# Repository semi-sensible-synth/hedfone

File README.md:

# hedfone eurorack module

_Simple stereo sum fixed panning headphone output in 2HP_

## Features

A 2HP headphone output with:

- Left and right mono inputs at eurorack levels (left+left, right+right, summed)
- First set of inputs panned hard left/right, second set are 'soft' left/right by ~6dB in the stereo field
- A 3.5mm TRS stereo output at line/headphone levels (0.4x gain, 5V -> 2.1 Vpp output)
- Dual audio op-amps per output channel to drive headphones
- Volume adjustment knob
- Internal pin header to take input from other modules (eg a mixer)

Intended to be used with 0HP attenuators if one of the summed inputs needs to be mixed/panned, or a 0HP passive mult if you need to put a mono signal into both channels.

## Design

For the headphone output, I used design similar to [this headphone amplifier](http://www.redcircuits.com/Page155.htm) using a dual op-amp (NE5532) per channel. The first op amp unit acts as a unity gain buffer, with a second non-inverting op amp in parallel to the output acting as voltage follower/buffer to allow it to drive more current. Other modules that use a similar technique include the [Befaco Out v3](https://www.befaco.org/out-v3/) headphone driver or [Forest Caver's Headphone Amp module](https://github.com/forestcaver/Analog-Voice/tree/master/AJH_Headphone_Amp).

The 3.5mm TRS stereo jack can be a [green Thonkiconn PJ366ST](https://www.thonk.co.uk/shop/green-stereo-thonkiconn-jacks-pj366st-x1/) or a [Tayda A-6115](https://www.taydaelectronics.com/3-5mm-stereo-enclosed-socket.html) bodged with a resistor wire.

## Version 1.1.2 - TODO
_(fixes for next revision)_

- Pot direction is reversed.
- Outer L/R pair are hard panned, inner pair are soft panned. This wasn't intentional, but actually makes sense (more like Nearness) - swap inner pair order and front panel to reflect that (so we have top to bottom L/L/R/R with the outer jacks hard panned)

## Version 1.1.1

Fix footprint for D1,D2 (SOD-523 -> SOD-323)

## Version 1.1

Made the second set of inputs 'soft' panned left and right by ~6dB.
Removed left->right normalling for mono (can't easily co-exist with the soft panning feature)

## Version 1.0

Initial release to production.

## License

[CERN-OHL-S-2.0](https://ohwr.org/cern_ohl_s_v2.txt) (*CERN Open Hardware License Version 2 - Strongly Reciprocal*), Andrew Perry, 2023.

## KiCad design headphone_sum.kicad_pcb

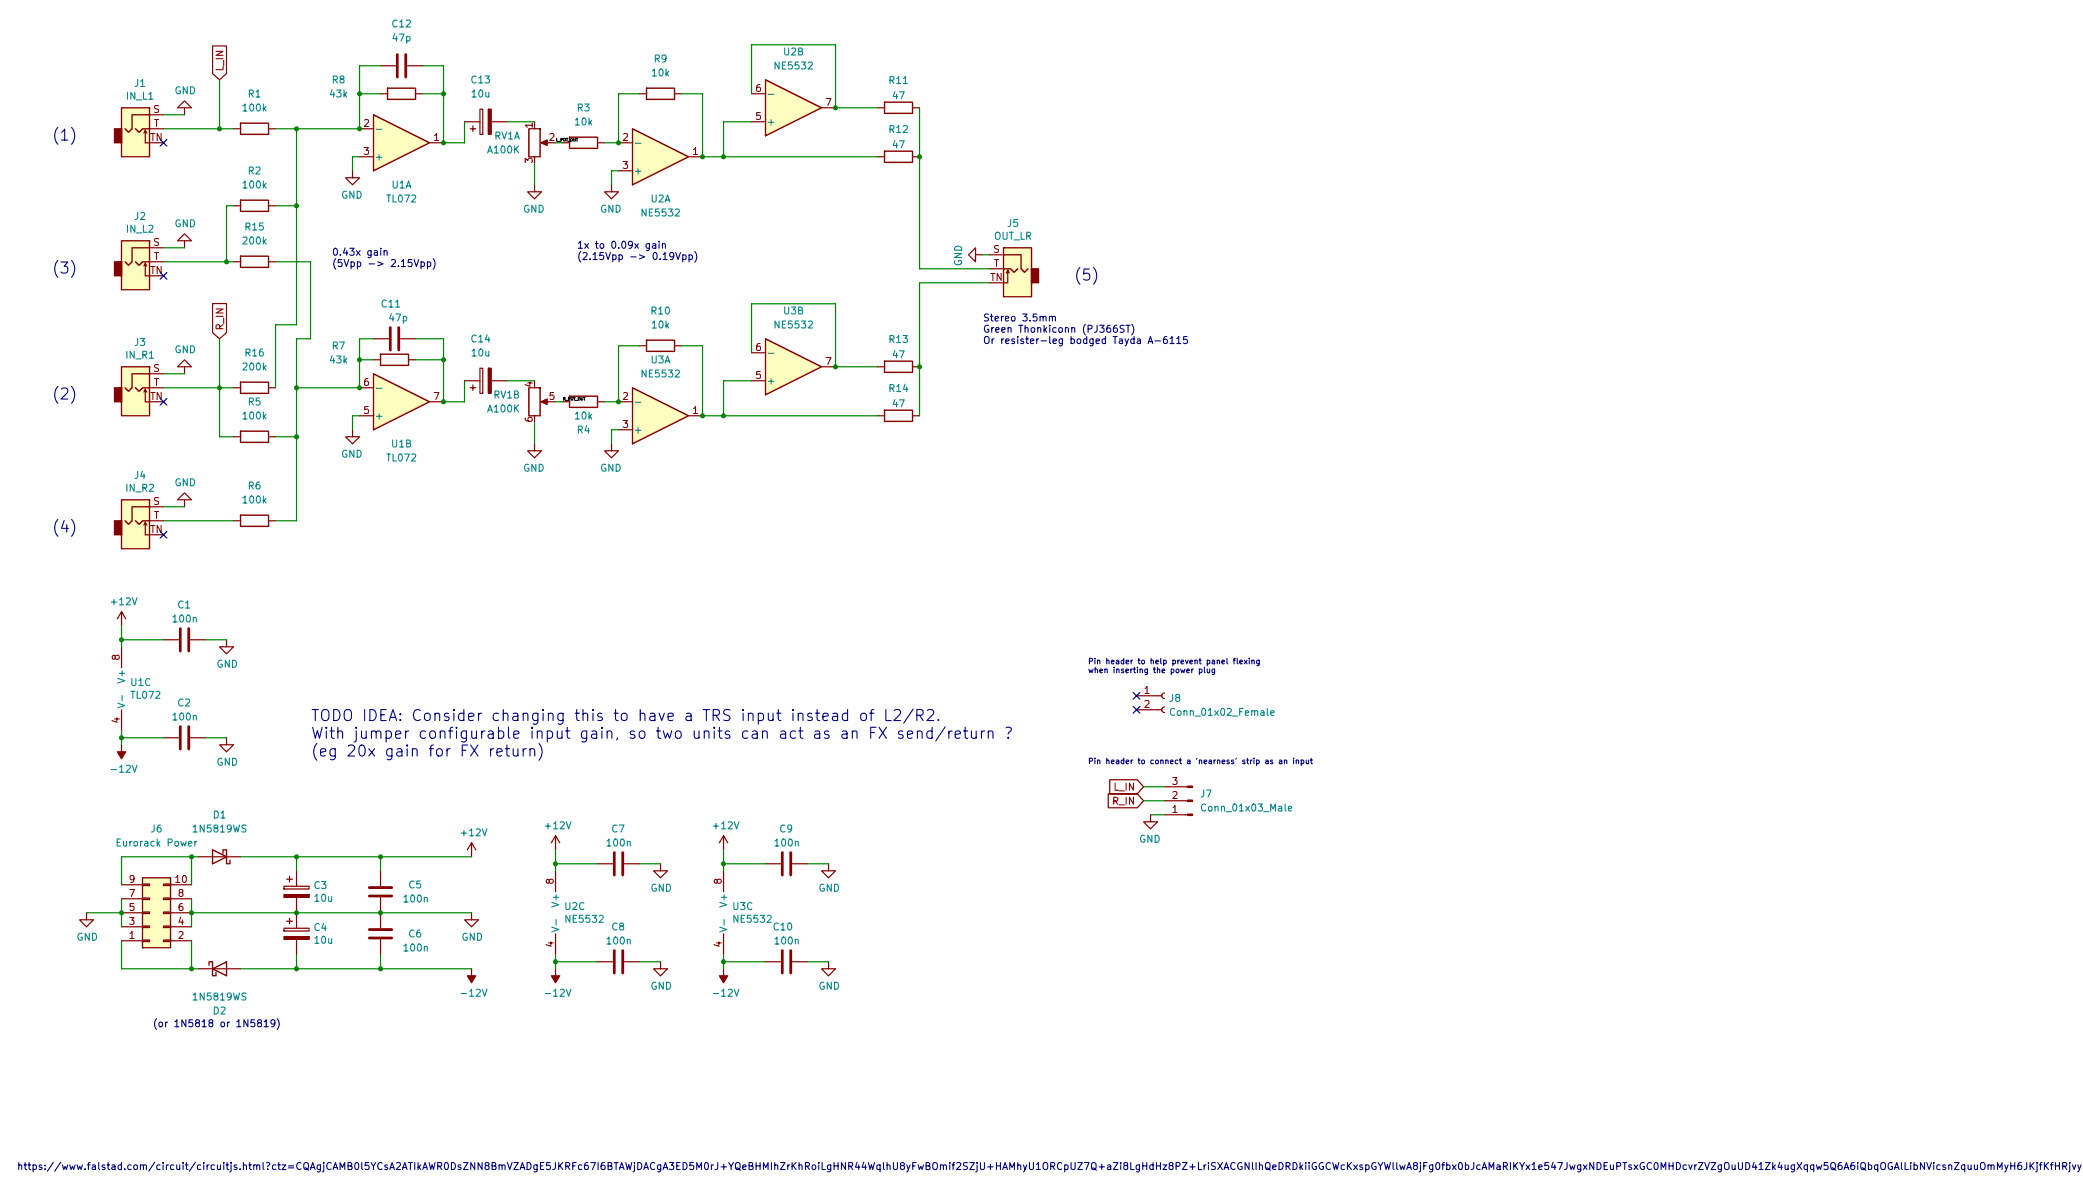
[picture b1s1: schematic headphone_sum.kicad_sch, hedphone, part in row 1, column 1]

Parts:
C1, C2, C5, C6, C7, C8, C9, C10: 100n; C_0603_1608Metric_Pad1.08x0.95mm_HandSolder; LCSC part number C14663
C3, C4, C13, C14: 10u; C_1206_3216Metric_Pad1.33x1.80mm_HandSolder; LCSC C13585
C11, C12: 47p; C_0603_1608Metric_Pad1.08x0.95mm_HandSolder; LCSC part number C1671
D1, D2: 1N5819WS; D_SOD-323; LCSC part number C191023
J1: IN_L1; 3.5mm_tip_switch_thonkiconn
J2: IN_L2; 3.5mm_tip_switch_thonkiconn
J3: IN_R1; 3.5mm_tip_switch_thonkiconn
J4: IN_R2; 3.5mm_tip_switch_thonkiconn
J5: OUT_LR; 3.5mm_tip_switch_thonkiconn
J6: Eurorack Power; PinHeader_2x05_P2.54mm_Vertical
J7: Conn_01x03_Male; PinHeader_1x03_P2.54mm_Vertical
J8: Conn_01x02_Female; PinHeader_1x02_P2.54mm_Vertical
R1, R2, R5, R6: 100k; R_0603_1608Metric_Pad0.98x0.95mm_HandSolder; LCSC part number C25803
R3, R4, R9, R10: 10k; R_0603_1608Metric_Pad0.98x0.95mm_HandSolder; LCSC part number C25804
R7, R8: 43k; R_0603_1608Metric_Pad0.98x0.95mm_HandSolder; LCSC part number C23172
R11, R12, R13, R14: 47; R_0603_1608Metric_Pad0.98x0.95mm_HandSolder; LCSC part number C23182
R15, R16: 200k; R_0603_1608Metric_Pad0.98x0.95mm_HandSolder; LCSC part number C25811
RV1: A100K; Potentiometer_Alpha_RD902F-40-00D_Dual_Vertical
U1: TL072; SOIC-8_3.9x4.9mm_P1.27mm; LCSC part number C6961
U2, U3: NE5532; SOIC-8_3.9x4.9mm_P1.27mm; LCSC part number C7426

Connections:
+12V: C1.1, C3.1, C5.2, C7.1, C9.1, D1.1 (K), U1.8 (V+), U2.8 (V+), U3.8 (V+)
-12V: C2.1, C4.2, C6.1, C8.1, C10.1, D2.2 (A), U1.4 (V-), U2.4 (V-), U3.4 (V-)
/L_POT_OUT: R3.2, RV1.2
/R_POT_OUT: R4.2, RV1.5
GND: C1.2, C2.2, C3.2, C4.1, C5.1, C6.2, C7.2, C8.2, C9.2, C10.2, J1.S, J2.S, J3.S, J4.S, J5.S, J6.3, J6.4, J6.5, J6.6, J6.7, J6.8, J7.1, RV1.3, RV1.6, U1.3 (+), U1.5 (+), U2.3 (+), U3.3 (+)
L_IN: J1.T, J7.3, R1.2
unnamed: C11.2, C14.1, R7.1, U1.7
unnamed: C12.2, C13.1, R8.1, U1.1
unnamed: C13.2, RV1.1
unnamed: C14.2, RV1.4
unnamed: D1.2 (A), J6.9, J6.10
unnamed: D2.1 (K), J6.1, J6.2
unnamed: J2.T, R2.2, R15.2
unnamed: J4.T, R6.2
unnamed: J5.T, R11.1, R12.1
unnamed: J5.TN, R13.1, R14.1
unnamed: C12.1, R1.1, R2.1, R8.2, R16.1, U1.2 (-)
unnamed: C11.1, R5.1, R6.1, R7.2, R15.1, U1.6 (-)
unnamed: R3.1, R9.2, U2.2 (-)
unnamed: R9.1, R12.2, U2.1, U2.5 (+)
unnamed: R11.2, U2.6 (-), U2.7
unnamed: R4.1, R10.2, U3.2 (-)
unnamed: R10.1, R14.2, U3.1, U3.5 (+)
unnamed: R13.2, U3.6 (-), U3.7
R_IN: J3.T, J7.2, R5.2, R16.2

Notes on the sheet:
(3)
(4)
Stereo 3.5mm Green Thonkiconn (PJ366ST) Or resister-leg bodged Tayda A-6115
Pin header to connect a 'nearness' strip as an input
(1)
TODO IDEA: Consider changing this to have a TRS input instead of L2/R2. With jumper configurable input gain, so two units can act as an FX send/return ? (eg 20x gain for FX return)
0.43x gain (5Vpp -> 2.15Vpp)
(or 1N5818 or 1N5819)
(2)
(5)
https://www.falstad.com/circuit/circuitjs.html?ctz=CQAgjCAMB0l5YCsA2ATIkAWR0DsZNN8BmVZADgE5JKRFc67I6BTAWjDACgA3ED5M0rJ+YQeBHMIhZrKhRoiLgHNR44WqlhU8yFwBOmif2SZjU+HAMhyU1ORCpUZ7Q+aZi8LgHdHz8PZ+LriSXACGNlIhQeDRDkiiGGCWcKxspGYWllwA8jFg0fbx0bJcAMaRIKYx1e547JwgxNDEuPTsxGC0MHDcvrZVZgOuUD41Zk4ugXqqw5Q6A6iQ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
1x to 0.09x gain (2.15Vpp -> 0.19Vpp)
Pin header to help prevent panel flexing when inserting the power plug

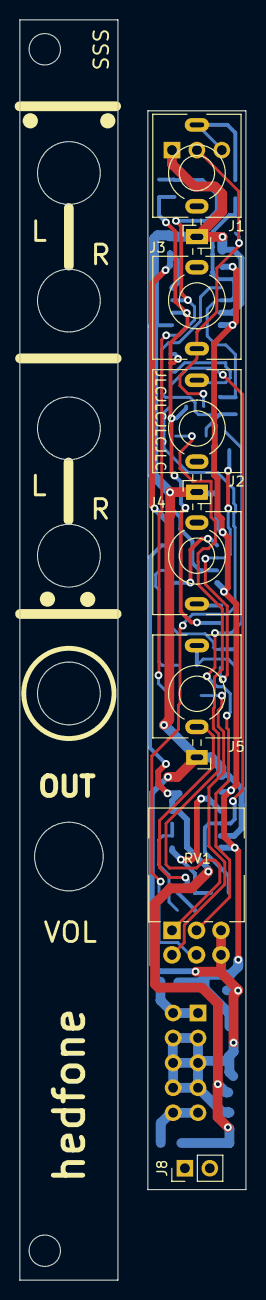
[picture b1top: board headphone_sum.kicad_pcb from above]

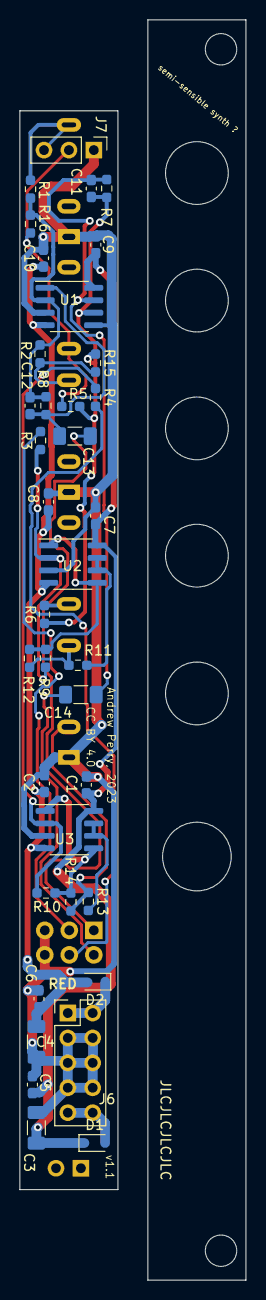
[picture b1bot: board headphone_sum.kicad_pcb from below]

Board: 2 copper layers, 23.1 x 128.5 mm, 46 parts (37 on the bottom side), 25 nets.

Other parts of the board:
M3 Screw: MountingHole_3.2mm_M3
M3 screw: locked; MountingHole_3.2mm_M3

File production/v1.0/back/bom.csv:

Designator,Footprint,Quantity,Value,LCSC Part #
"C1, C10, C2, C5, C6, C7, C8, C9",0603,8,100n,C14663
"C11, C12",0603,2,47p,C1671
"C13, C14, C3, C4",1206,4,10u,C13585
"D1, D2",D_SOD-523,2,1N5819WS,C191023
J1,3.5mm_tip_switch_thonkiconn,1,IN_L1,
J2,3.5mm_tip_switch_thonkiconn,1,IN_L2,
J3,3.5mm_tip_switch_thonkiconn,1,IN_R1,
J4,3.5mm_tip_switch_thonkiconn,1,IN_R2,
J5,3.5mm_tip_switch_thonkiconn,1,OUT_LR,
J6,PinHeader_2x05_P2.54mm_Vertical,1,Eurorack Power,
J7,PinHeader_1x03_P2.54mm_Vertical,1,Conn_01x03_Male,
J8,PinHeader_1x02_P2.54mm_Vertical,1,Conn_01x02_Female,
"R1, R2, R5, R6",0603,4,100k,C25803
"R10, R3, R4, R9",0603,4,10k,C25804 
"R11, R12, R13, R14",0603,4,47,C23182
"R7, R8",0603,2,43k,C23172
RV1,Potentiometer_Alpha_RD902F-40-00D_Dual_Vertical,1,A100K,
U1,SOIC-8_3.9x4.9mm_P1.27mm,1,TL072,C6961
"U2, U3",SOIC-8_3.9x4.9mm_P1.27mm,2,NE5532,C7426

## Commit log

2023-08-06 Initial commit, schematic and PCB layout
2023-08-06 Generate gerbers and BOM for front and back
2023-08-29 Remove duplicate front/back file, old KiCad files.
2023-08-29 Generate gerbers, production files for v1.1
2023-09-09 BOM and position file fixes
2023-09-10 v1.1.1, fix some LCSC part numbers, fix D1,D2 footprint
2023-10-22 Add TODOs for next revision.
2023-10-22 Change license to CERN-OHL-S-2.0

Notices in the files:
headphone_sum.kicad_pcb:
CC BY 4.0
